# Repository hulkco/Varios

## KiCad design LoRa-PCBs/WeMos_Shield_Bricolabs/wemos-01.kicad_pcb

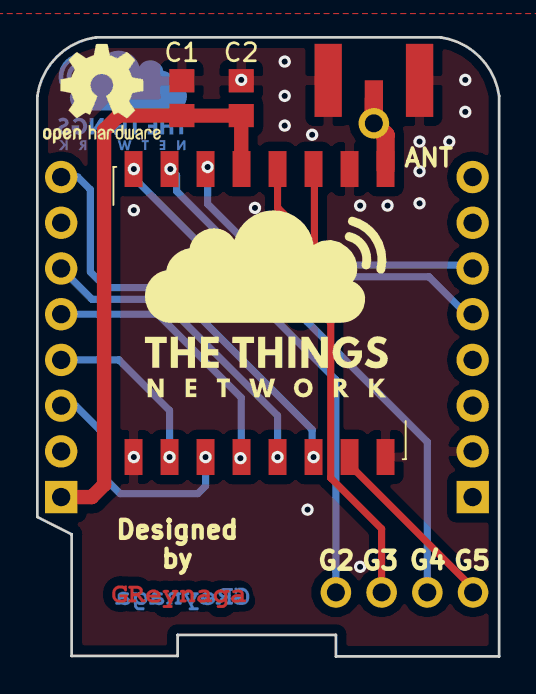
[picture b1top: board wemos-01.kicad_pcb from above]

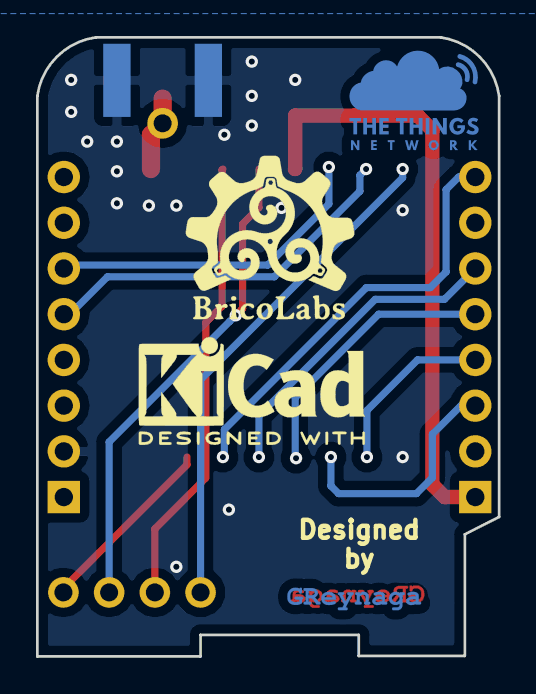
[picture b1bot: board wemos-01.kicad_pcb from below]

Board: 2 copper layers, 25.7 x 34.4 mm, 14 parts (5 on the bottom side), 14 nets.

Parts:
A2: ANT; SMA_EDGELAUNCH_UFL_WeMos_Lora
C1: 1u; C_0805_2012Metric_Pad1.29x1.40mm_HandSolder
C2: 10u; C_0805_2012Metric_Pad1.29x1.40mm_HandSolder
GBSilk***: LOGO; greynaga6-2-Mask
GBSilk***#2: LOGO; greynaga6-2-Mask
GS***: v; greynaga6-2-Cooper
GS***#2: v; greynaga6-2-Cooper
J1: Conn_01x04; PinSocket_1x04_P2.54mm_WeMos
J2: Conn_01x01; PinSocket_1x01_P2.54mm_WeMos
P1, P2: CONN_01X08; D1_mini_Pin_Header
U1: RFM95W-915S2; HOPERF_RFM9XW_SMD_WeMos
svg2mod: G***; ttn_logoCu1
svg2mod#2: G***; ttn_logo3

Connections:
/+3.3V: C1.1, C2.1, P2.1, U1.13
/D0: P2.6, U1.5
/D1: P1.6, U1.14
/D2: P1.5, U1.15
/D5: P2.5, U1.4
/D6: P2.4, U1.2
/D7: P2.3, U1.3
/G2: J1.1, U1.16
/G3: J1.2, U1.11
/G4: J1.3, U1.12
/G5: J1.4, U1.7
/GND: A2.2, A2.3, A2.4, A2.5, C1.2, C2.2, P1.2, U1.1, U1.8, U1.10
/RST: P2.8, U1.6
unnamed: A2.1, J2.1, U1.9

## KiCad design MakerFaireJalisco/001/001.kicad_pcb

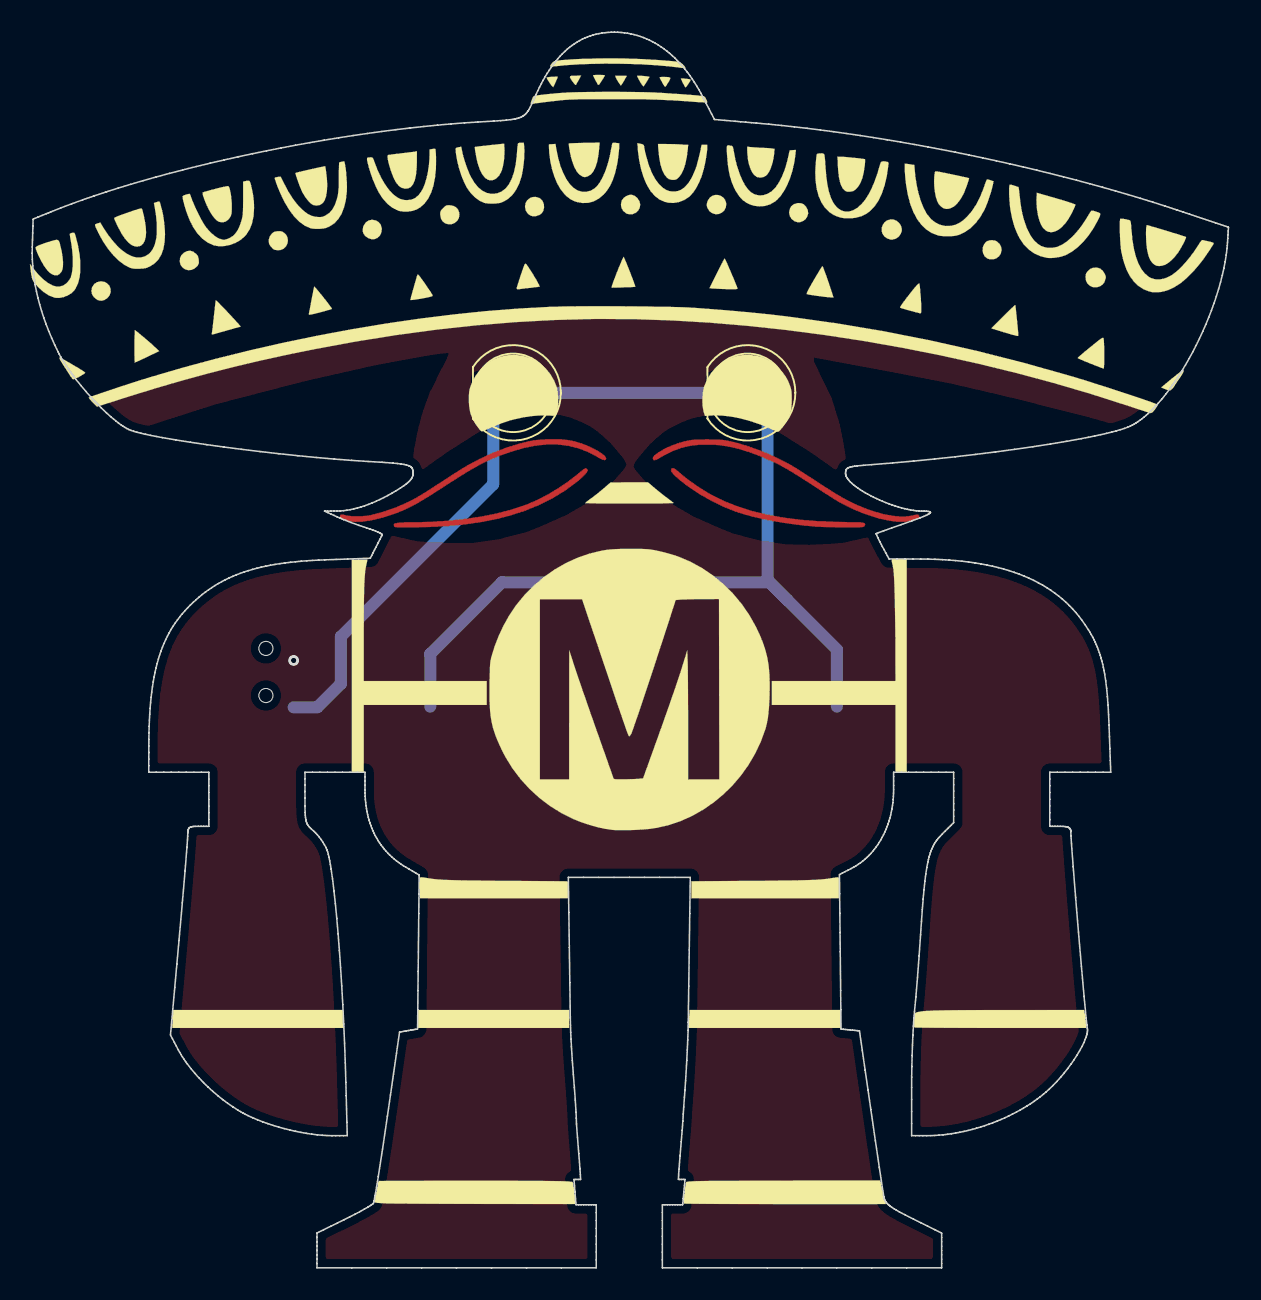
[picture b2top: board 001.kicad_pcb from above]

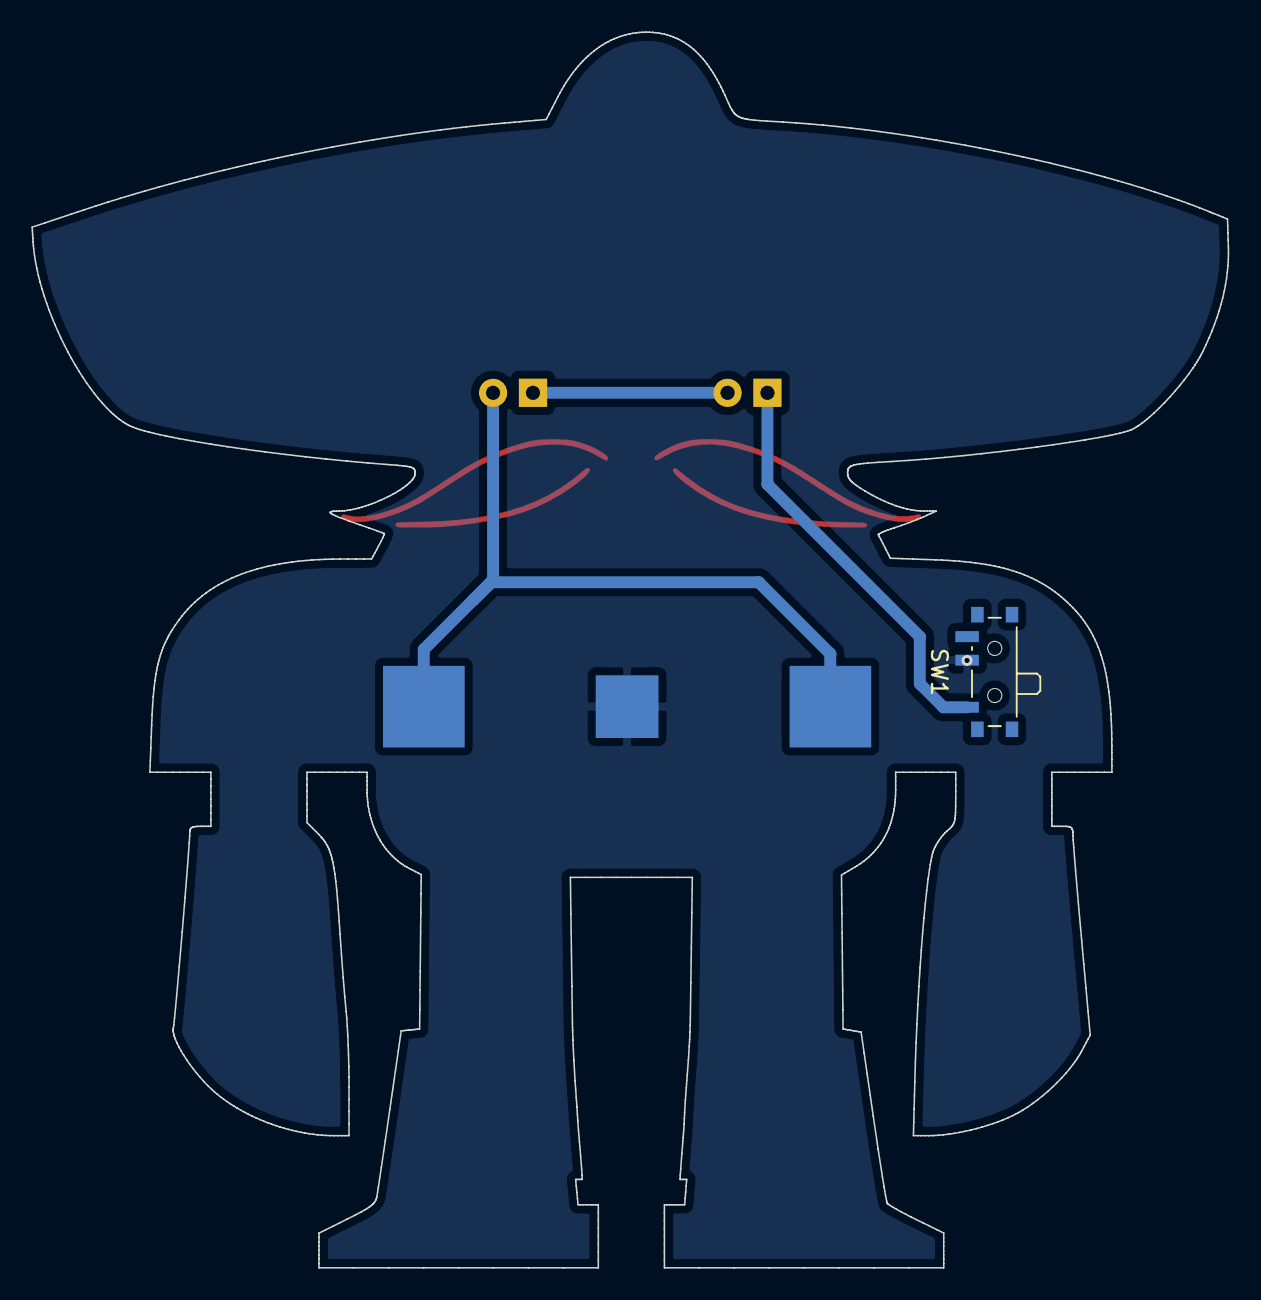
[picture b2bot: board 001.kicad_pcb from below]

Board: 2 copper layers, 76.2 x 78.7 mm, 5 parts (2 on the bottom side), 4 nets.

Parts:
BT1: Battery_3V_Coin; WA-BCMC
D1, D2: LED; LED_D5.0mm_FlatTop
SW1: SW_SPDT; SW_SPDT_PCM12
U1: MF-Jalisco; MF-Jalisco-001

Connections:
+3V3: BT1.1, D2.2
GND: BT1.2, SW1.2
unnamed: D1.1, SW1.1
unnamed: D1.2, D2.1

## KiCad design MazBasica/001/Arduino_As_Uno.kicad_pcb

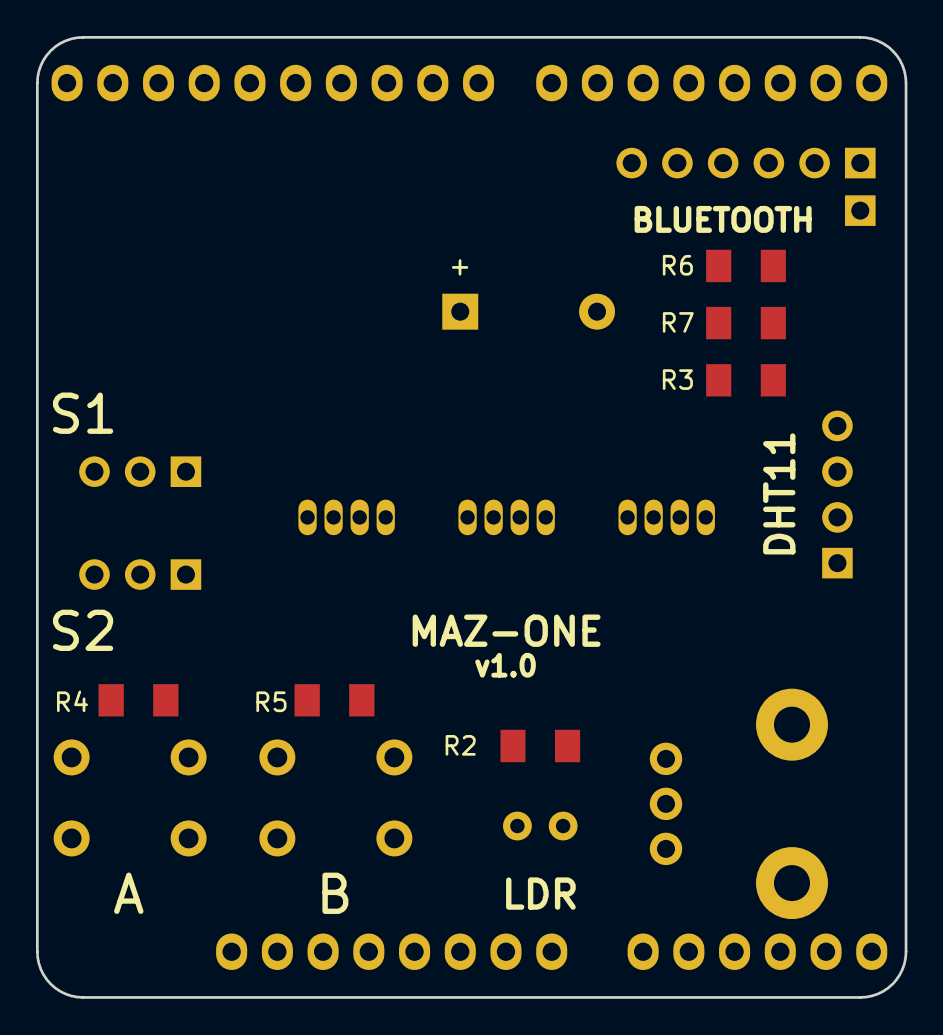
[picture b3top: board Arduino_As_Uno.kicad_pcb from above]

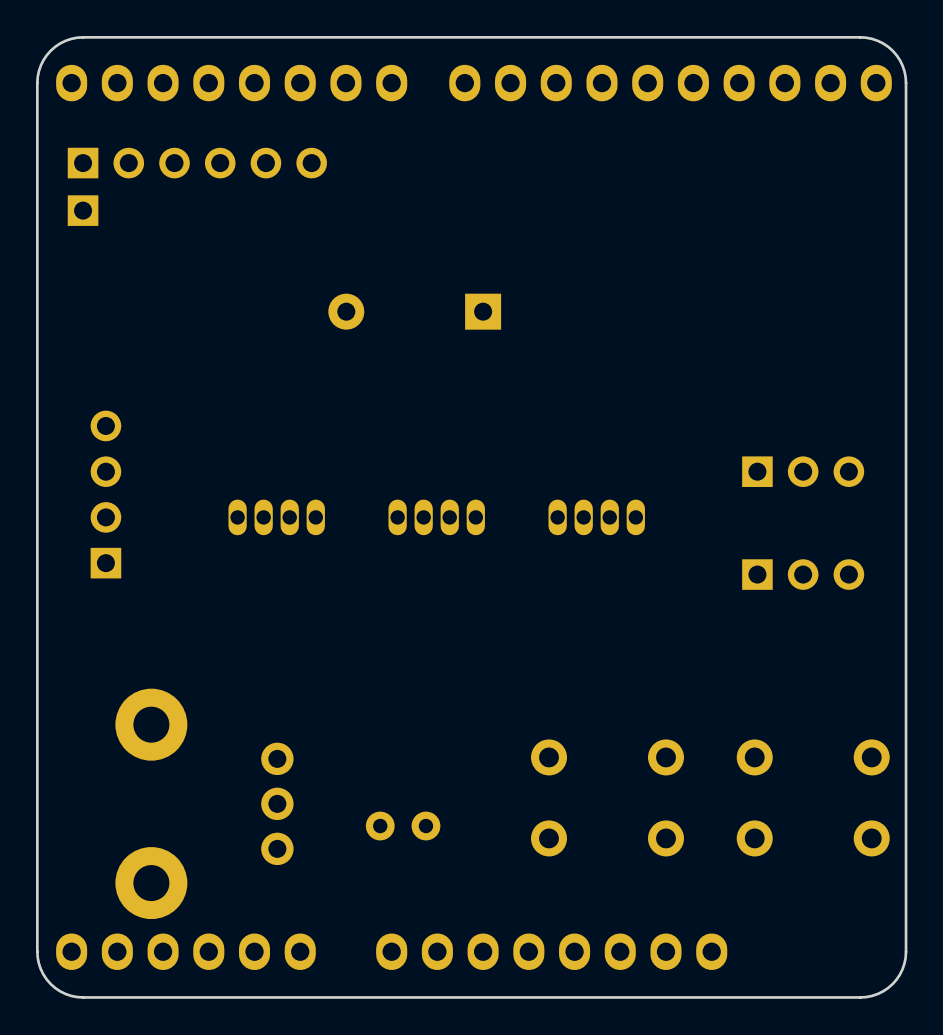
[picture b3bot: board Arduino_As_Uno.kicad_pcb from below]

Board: 2 copper layers, 48.3 x 53.3 mm, 23 parts (4 on the bottom side), 19 nets, no tracks yet.

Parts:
BZ1: Buzzer; Buzzer_12x9.5RM7.6
J1: CONN_01X04; PinHeader_1x04_P2.54mm_Vertical
J2, J3: CONN_01X03; PinHeader_1x03_P2.54mm_Vertical
J4: CONN_01X06; PinHeader_1x06_P2.54mm_Vertical
J5: CONN_01X01; PinHeader_1x01_P2.54mm_Vertical
LDR: RES_PHOTO_LDR; R_LDR_4.9x4.2mm_P2.54mm_Vertical
LED1, LED2, LED3: PL9823
P1: Power; Socket_Strip_Arduino_1x08
P2: Analog; Socket_Strip_Arduino_1x06
P3: Digital; Socket_Strip_Arduino_1x10
P4: Digital; Socket_Strip_Arduino_1x08
R2, R3: 10k; R_1206_3216Metric_Pad1.39x1.80mm_HandSolder
R4, R5: 330; R_1206_3216Metric_Pad1.39x1.80mm_HandSolder
R6: 2k; R_1206_3216Metric_Pad1.39x1.80mm_HandSolder
R7: 1k; R_1206_3216Metric_Pad1.39x1.80mm_HandSolder
RV1: POT; Potentiometer_Bourns_PTV09A-1_Single_Vertical
SW1, SW2: SW_Push; SW_PUSH_6mm

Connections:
+5V: J1.1, J2.2, J3.2, J4.2, LED1.2, LED2.2, LED3.2, P1.5, R2.1, R3.2, RV1.3, SW1.1, SW2.1
/0(Rx): J4.4, P4.8
/1(Tx): P4.7, R6.1, R7.1
/2: J1.2, P4.6, R3.1
/3(**): BZ1.1, P4.5
/5(**): J2.1, P4.3
/6(**): J3.1, P4.2
/9(**): LED1.1, P3.9
/A0: LDR.1, P2.1, R2.2
/A1: P2.2, RV1.2
/A2: P2.3, R4.2, SW1.2
/A3: P2.4, R5.2, SW2.2
/A4(SDA): P2.5, P3.2
/A5(SCL): P2.6, P3.1
/Reset: J5.1, P1.3
GND: BZ1.2, J1.4, J2.3, J3.3, J4.3, LDR.2, LED1.3, LED2.3, LED3.3, P1.6, P1.7, P3.4, R4.1, R5.1, R6.2, RV1.1
unnamed: J4.5, R7.2
unnamed: LED1.4, LED2.1
unnamed: LED2.4, LED3.1

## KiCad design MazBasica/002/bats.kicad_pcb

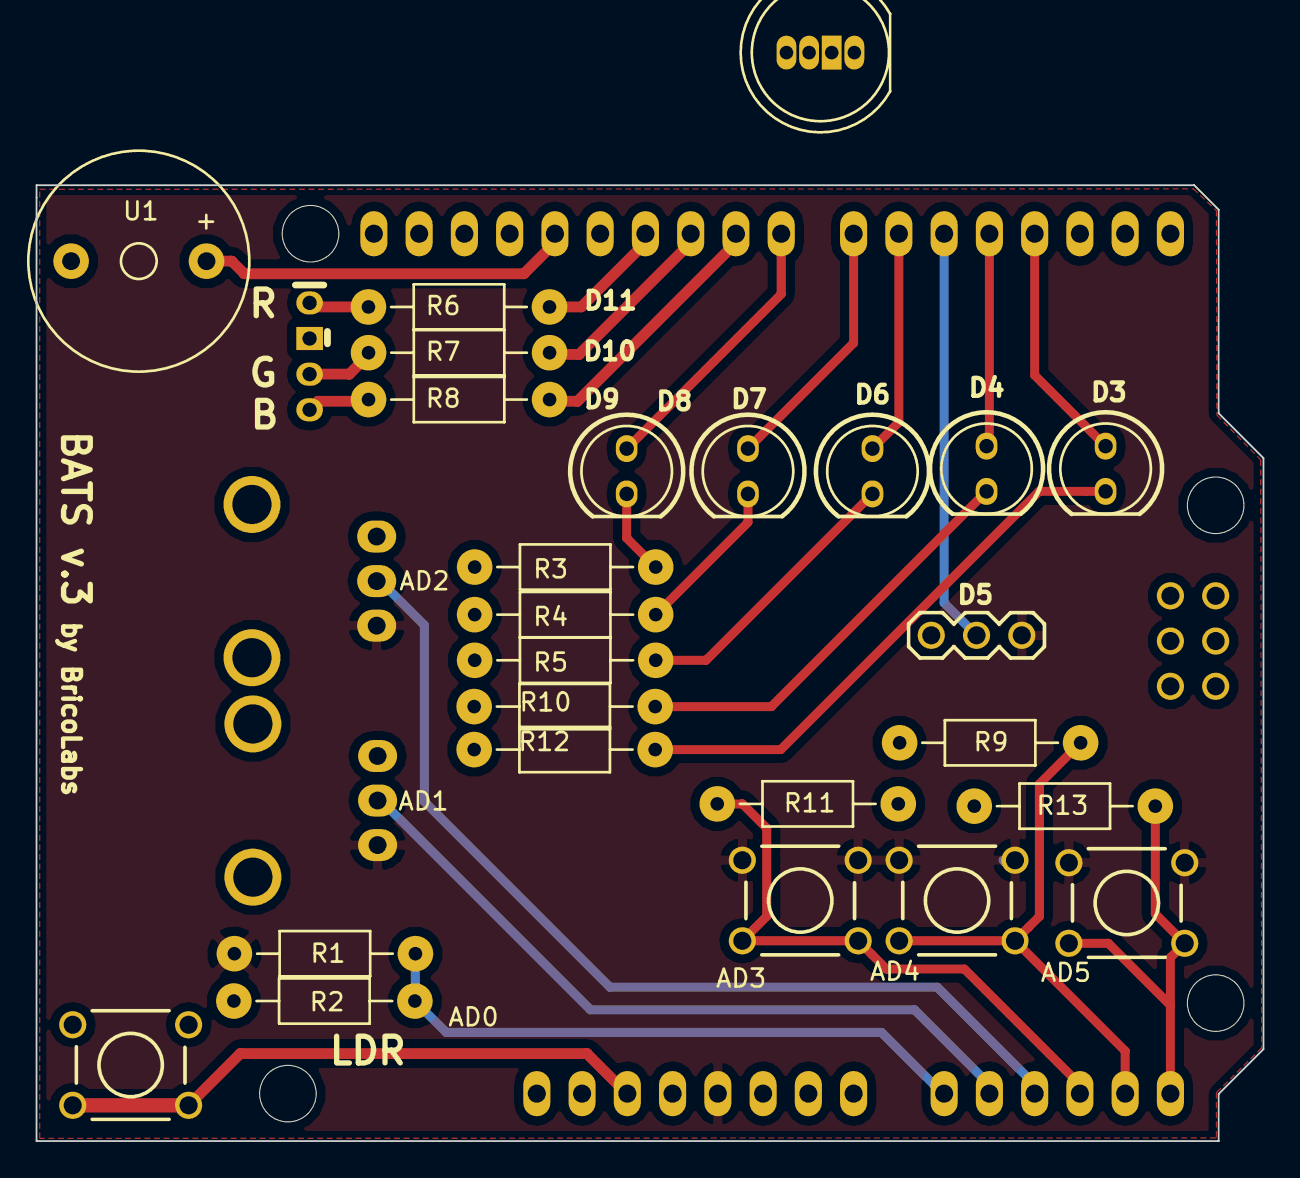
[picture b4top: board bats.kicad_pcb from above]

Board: 2 copper layers, 68.9 x 53.6 mm, 28 parts (0 on the bottom side), 27 nets.

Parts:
LED1: Red LED; LED-5MM_easy_soldering
LED2: Yellow LED; LED-5MM_easy_soldering
LED3: Green LED; LED-5MM_easy_soldering
LED4: LED_RGB_COM_K; LED-RGB-8MM-COM-K-MINIMAL_easy_soldering
LED5, LED6: LED; LED-5MM_easy_soldering
P1: SERVO; 1X03
R1: RES_PHOTO_LDR; Resistor_Horizontal_SmallHole_RM10mm
R2, R9, R11, R13: 10K; Resistor_Horizontal_SmallHole_RM10mm
R3, R4, R5, R6, R7, R8, R10, R12: 220; Resistor_Horizontal_SmallHole_RM10mm
SHIELD1: ARDUINO_SHIELD
SW1: RESET; SW_PUSHBUTTON_PTH
SW2: SHOT; SW_PUSHBUTTON_PTH
SW4: LEFT; SW_PUSHBUTTON_PTH
SW6: RIGHT; SW_PUSHBUTTON_PTH
U1: BUZZER; Buzzer_12x9.5RM7.6
VR1, VR2: POT; POT_RV09_VERT_easySoldering

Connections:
/AD0: R1.2, R2.1, SHIELD1.AD0
/AD1: SHIELD1.AD1, VR1.W
/AD2: SHIELD1.AD2, VR2.W
/AD3: R11.1, SHIELD1.AD3, SW4.2
/AD4: R9.1, SHIELD1.AD4, SW2.2
/AD5: R13.1, SHIELD1.AD5, SW6.2
/ARD3: LED6.A, SHIELD1.3
/ARD4: LED5.A, SHIELD1.4
/ARD5: P1.2, SHIELD1.5
/ARD6: LED3.A, SHIELD1.6
/ARD7: LED2.A, SHIELD1.7
/ARD8: LED1.A, SHIELD1.8
/ARD9: R8.2, SHIELD1.9
/ARD10: R7.2, SHIELD1.10
/ARD11: R6.2, SHIELD1.11
/ARD13: SHIELD1.13, U1.2
/VCC: P1.1, R1.1, SHIELD1.5V, SW2.1, SW4.1, SW6.1, VR1.1, VR2.1
GND: LED4.K, P1.3, R2.2, R3.2, R4.2, R5.2, R9.2, R10.2, R11.2, R12.2, R13.2, SHIELD1.GND1, SHIELD1.GND2, SHIELD1.GND3, SW1.1, U1.1, VR1.2, VR2.2
unnamed: LED1.K, R3.1
unnamed: LED2.K, R4.1
unnamed: LED3.K, R5.1
unnamed: LED4.AB, R8.1
unnamed: LED4.AG, R7.1
unnamed: LED4.AR, R6.1
unnamed: LED5.K, R10.1
unnamed: LED6.K, R12.1
unnamed: SHIELD1.RST, SW1.2
